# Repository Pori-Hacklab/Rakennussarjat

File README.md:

# Rakennussarjat
Tänne voi upata TOIMIVIKSI TODETTUJA kytkentöjä.
Näistä tehdään sitten piirilevyjä joko itse tai kiinanpoikien toimesta.

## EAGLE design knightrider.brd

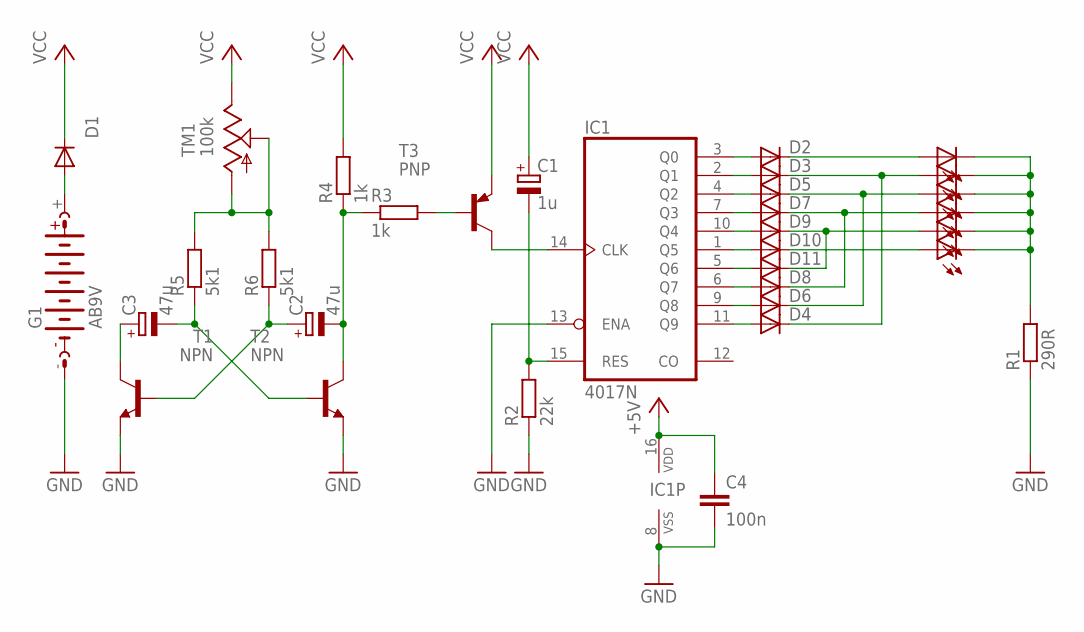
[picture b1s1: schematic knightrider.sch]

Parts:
C1: 1u; E2,5-6
C2, C3: 47u; E2,5-6
C4: 100n; C050-025X075
D1: 1N4148; DO35-7
D2, D3, D4, D5, D6, D7, D8, D9, D10, D11: 1N4148DO35-7; DO35-7
G1: AB9V
IC1: 4017N; DIL16
LED1, LED2, LED3, LED4, LED5, LED6: LED5MM
R1: 290R; 0204/7
R2: 22k; 0204/7
R3, R4: 1k; 0204/7
R5, R6: 5k1; 0204/7
T1, T2: NPN; TO92-EBC
T3: PNP; TO92-EBC
TM1: 100k; 6MM

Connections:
+5V: C1.+, C4.1, D1.C, IC1.16 (VDD), R4.2, T3.E, TM1.E
GND: C4.2, G1.-, IC1.8 (VSS), IC1.13 (ENA), R1.1, R2.1, T1.E, T2.E
unnamed: D2.A, IC1.3 (Q0)
unnamed: D3.A, IC1.2 (Q1)
unnamed: D4.A, IC1.11 (Q9)
unnamed: D5.A, IC1.4 (Q2)
unnamed: D6.A, IC1.9 (Q8)
unnamed: D7.A, IC1.7 (Q3)
unnamed: D8.A, IC1.6 (Q7)
unnamed: D9.A, IC1.10 (Q4)
unnamed: D10.A, IC1.1 (Q5)
unnamed: D11.A, IC1.5 (Q6)
unnamed: D3.C, D4.C, LED2.A
unnamed: D5.C, D6.C, LED3.A
unnamed: D7.C, D8.C, LED4.A
unnamed: D9.C, D11.C, LED5.A
unnamed: D2.C, LED1.A
unnamed: D10.C, LED6.A
unnamed: LED1.K (C), LED2.K (C), LED3.K (C), LED4.K (C), LED5.K (C), LED6.K (C), R1.2
unnamed: IC1.14 (CLK), T3.C
unnamed: C1.-, IC1.15 (RES), R2.2
unnamed: D1.A, G1.+
unnamed: C3.+, T1.C
unnamed: C3.-, R5.1, T2.B
unnamed: R3.2, T3.B
unnamed: C2.-, R3.1, R4.1, T2.C
unnamed: C2.+, R6.1, T1.B
unnamed: R5.2, R6.2, TM1.A, TM1.S

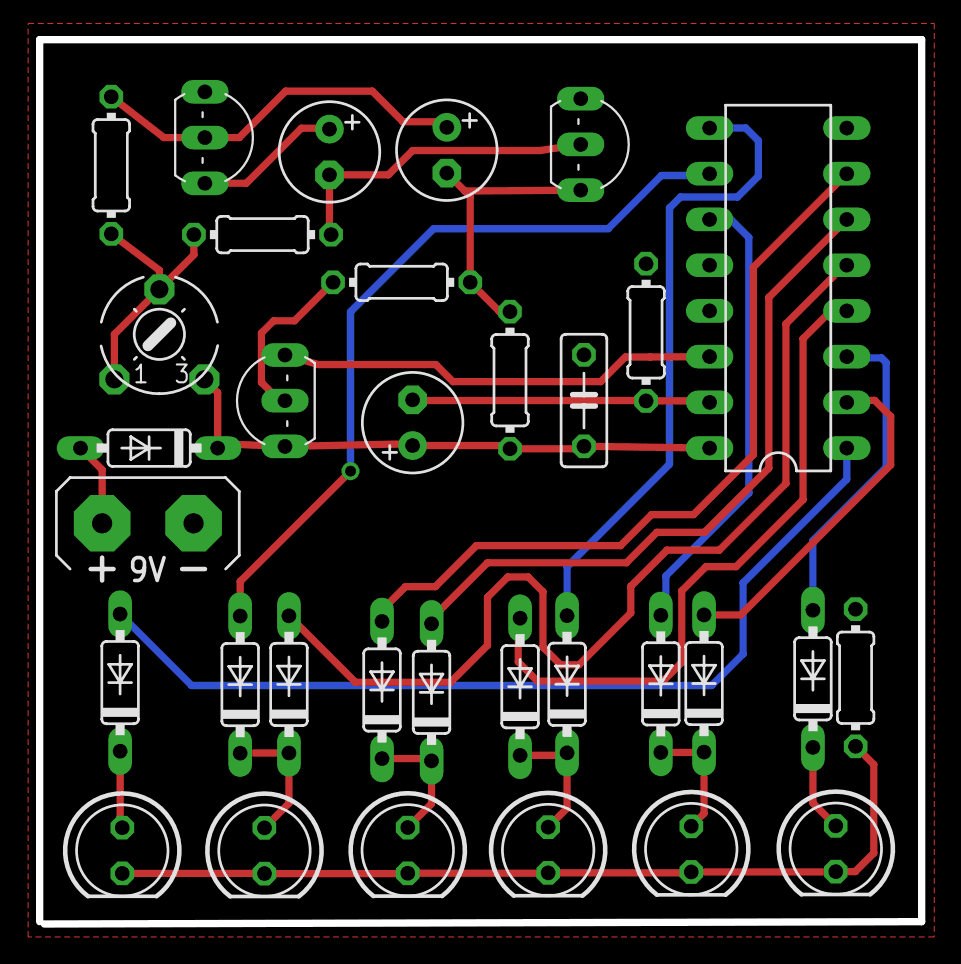
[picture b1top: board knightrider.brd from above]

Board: 2 copper layers, 49.0 x 49.1 mm, 33 parts (0 on the bottom side), 28 nets.

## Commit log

2015-08-05 :circus_tent: Added .gitattributes
2015-08-11 no message
